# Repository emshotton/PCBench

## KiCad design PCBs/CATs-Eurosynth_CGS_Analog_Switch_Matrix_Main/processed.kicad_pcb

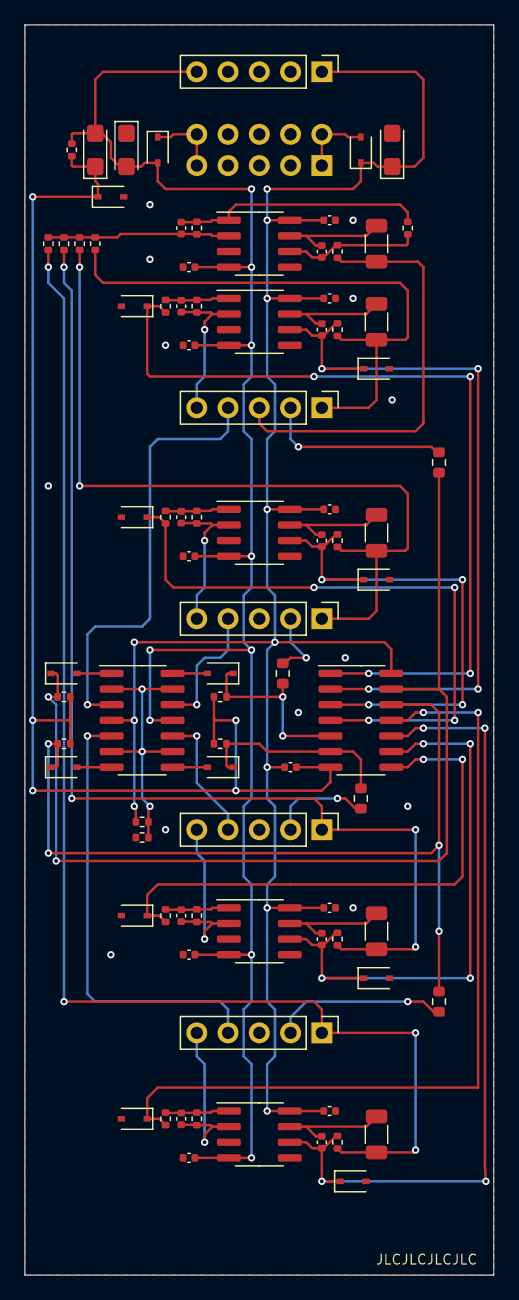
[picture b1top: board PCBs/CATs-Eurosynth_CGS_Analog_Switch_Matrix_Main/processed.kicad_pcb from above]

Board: 2 copper layers, 38.1 x 101.6 mm, 87 parts (1 on the bottom side), 52 nets.

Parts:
C1, C2, C3, C4, C13, C14, C15, C16, C21, C23: 47p; C_0402_1005Metric
C5, C6, C22: 10µF; CP_EIA-3216-18_Kemet-A
C7, C8, C9, C10, C11, C12, C17, C18, C19, C20, C24: 100n; C_0402_1005Metric
D1, D2: B5817WS; D_SOD-323
D3, D4, D5, D6, D7, D8, D9, D10, D11, D12, D13, D14, D15: 1N4148; D_SOD-323
J1: Power; Power_2x5_Vertical
J2: 1_COM; PinHeader_1x05_P2.54mm_Vertical
J3: 2; PinHeader_1x05_P2.54mm_Vertical
J4: 3; PinHeader_1x05_P2.54mm_Vertical
J5: 4; PinHeader_1x05_P2.54mm_Vertical
J6: POWER; PinHeader_1x05_P2.54mm_Vertical
R1, R2, R3, R4, R5, R6, R7, R8, R9, R10, R11, R12, R17, R19, R20, R21, R22, R23, R24, R25, R26, R31, R33, R34: 100k; R_0402_1005Metric
R13, R14, R15, R16, R35: 1k; R_1206_3216Metric
R18: 10k; R_0402_1005Metric
R27, R28, R29, R30: 1k; R_0603_1608Metric
R32: 1k; R_0402_1005Metric
U1, U2, U3, U4, U7: TL072CDT; SOIC-8_3.9x4.9mm_P1.27mm
U5: CD4066BM/TR; SOIC-14_3.9x8.7mm_P1.27mm
U6: TL074IDT; SOIC-14_3.9x8.7mm_P1.27mm

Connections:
+12V: C5.1, C7.2, C9.2, C11.2, C17.2, C19.2, C24.2, D1.1, J6.1, R17.2, U1.8, U2.8, U3.8, U4.8, U5.14, U6.4, U7.8
-12V: C6.2, C8.1, C10.1, C12.1, C18.1, C20.1, C22.2, D2.2, J6.5, R32.1, U1.4, U2.4, U3.4, U4.4, U6.11, U7.4
B1: D11.1, R19.2, R27.1, U5.13
B2: D12.1, R20.2, R28.1, U5.5
B3: D13.1, R21.2, R29.1, U5.6
B4: D14.1, R22.2, R30.1, U5.12
C1: J2.4, U6.3
C2: J3.4, U6.12
C3: J4.4, U6.10
C4: J5.4, U6.5
COMOUT: J2.3, R34.1, R35.1
GND: C5.2, C6.1, C7.1, C8.2, C9.1, C10.2, C11.1, C12.2, C17.1, C18.2, C19.1, C20.2, D3.2, D4.2, D5.2, D6.2, D7.2, D8.2, D9.2, D10.2, D15.2, J1.GND, J3.3, J4.3, J5.3, J6.2, J6.3, J6.4, R18.1, U1.3, U1.5, U2.3, U2.5, U3.3, U3.5, U4.3, U4.5, U7.3, U7.5
I1: C1.2, J2.5, R1.2, U1.2
I2: C2.2, J3.5, R2.2, U2.2
I3: C3.2, J4.5, R3.2, U3.2
I4: C4.2, J5.5, R4.2, U4.2
L1: J2.2, R27.2
L2: J3.2, R28.2
L3: J4.2, R29.2
L4: J5.2, R30.2
unnamed: C1.1, R1.1, R5.2, U1.1
unnamed: C2.1, R2.1, R6.2, U2.1
unnamed: C3.1, R3.1, R7.2, U3.1
unnamed: C4.1, R4.1, R8.2, U4.1
unnamed: C13.1, R13.2, U1.7
unnamed: C13.2, D7.1, R9.2, U1.6, U5.2
unnamed: C14.1, R14.2, U2.7
unnamed: C14.2, D8.1, R10.2, U2.6, U5.3
unnamed: C15.1, R15.2, U3.7
unnamed: C15.2, D9.1, R11.2, U3.6, U5.9
unnamed: C16.1, R16.2, U4.7
unnamed: C16.2, D10.1, R12.2, U4.6, U5.10
unnamed: C21.1, R31.1, R33.2, U7.1
unnamed: C21.2, R23.1, R24.1, R25.1, R26.1, R31.2, U7.2
unnamed: C23.1, R35.2, U7.7
unnamed: C23.2, R33.1, R34.2, U7.6
unnamed: D1.2, J1.+12V
unnamed: D2.1, J1.-12V
unnamed: D3.1, R5.1, U5.1
unnamed: D4.1, R6.1, U5.4
unnamed: D5.1, R7.1, U5.8
unnamed: D6.1, R8.1, U5.11
unnamed: D11.2, U6.1
unnamed: D12.2, U6.14
unnamed: D13.2, U6.8
unnamed: D14.2, U6.7
unnamed: R17.1, R18.2, U6.2, U6.6, U6.9, U6.13
O1: J2.1, R9.1, R13.1, R23.2
O2: J3.1, R10.1, R14.1, R24.2
O3: J4.1, R11.1, R15.1, R25.2
O4: J5.1, R12.1, R16.1, R26.2
VEE: C22.1, C24.1, D15.1, R19.1, R20.1, R21.1, R22.1, R32.2, U5.7

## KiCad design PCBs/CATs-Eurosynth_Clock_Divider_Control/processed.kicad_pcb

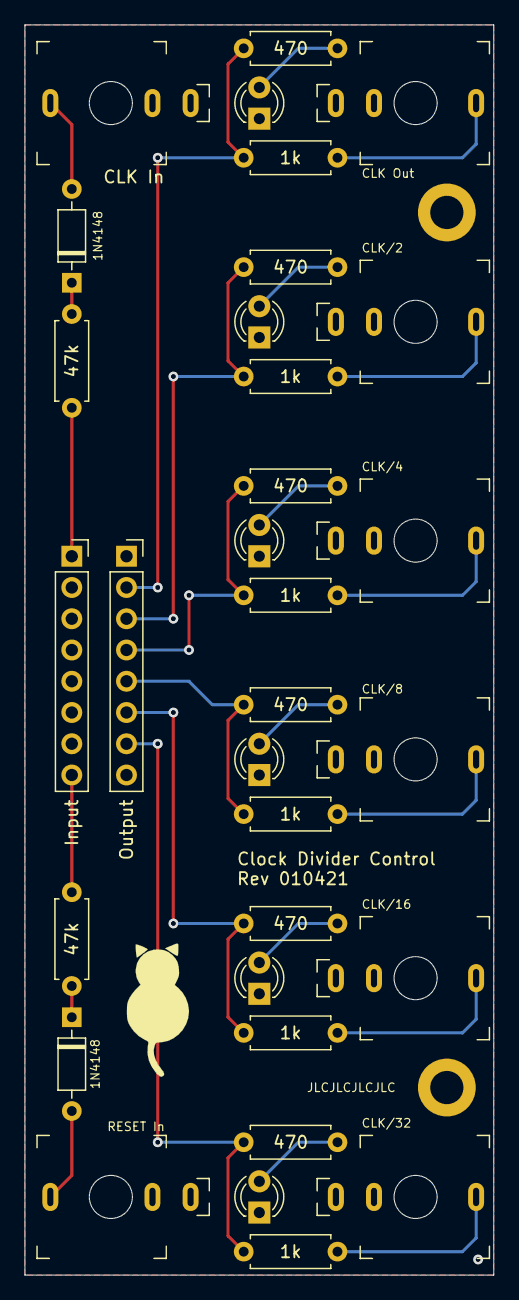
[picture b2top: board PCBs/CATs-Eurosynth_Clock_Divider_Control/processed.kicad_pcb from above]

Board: 2 copper layers, 38.1 x 101.6 mm, 34 parts (0 on the bottom side), 25 nets.

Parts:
D1, D2: 1N4148; D_DO-35_SOD27_P7.62mm_Horizontal
D4, D5, D6, D7, D8, D9: LED; LED_D3.0mm
H1, H2: MountingHole_Pad; MountingHole_2.7mm_M2.5_DIN965_Pad
J1: CLK In; PJ-301-M-12
J2: RESET In; PJ-301-M-12
J3: Input; PinSocket_1x08_P2.54mm_Vertical
J4: CLK/2; PJ-301-M-12
J5: CLK/4; PJ-301-M-12
J6: CLK/8; PJ-301-M-12
J7: CLK/16; PJ-301-M-12
J8: CLK/32; PJ-301-M-12
J9: CLK Out; PJ-301-M-12
J10: Output; PinSocket_1x08_P2.54mm_Vertical
R3, R4: 47k; R_Axial_DIN0207_L6.3mm_D2.5mm_P7.62mm_Horizontal
R17, R19, R21, R23, R25, R28: 1k; R_Axial_DIN0207_L6.3mm_D2.5mm_P7.62mm_Horizontal
R18, R20, R22, R24, R26, R29: 470; R_Axial_DIN0207_L6.3mm_D2.5mm_P7.62mm_Horizontal

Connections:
GND: D4.1, D5.1, D6.1, D7.1, D8.1, D9.1, H1.1, H2.1, J1.S, J2.S, J3.2, J3.3, J3.4, J3.5, J3.6, J3.7, J4.S, J5.S, J6.S, J7.S, J8.S, J9.S, J10.1, J10.8
unnamed: D1.1, R3.2
unnamed: D1.2, J1.T
unnamed: D2.1, R4.2
unnamed: D2.2, J2.T
unnamed: D4.2, R18.2
unnamed: D5.2, R20.2
unnamed: D6.2, R22.2
unnamed: D7.2, R24.2
unnamed: D8.2, R26.2
unnamed: D9.2, R29.2
unnamed: J3.1, R3.1
unnamed: J3.8, R4.1
unnamed: J4.T, R17.2
unnamed: J5.T, R19.2
unnamed: J6.T, R21.2
unnamed: J7.T, R23.2
unnamed: J8.T, R25.2
unnamed: J9.T, R28.2
unnamed: J10.2, R28.1, R29.1
unnamed: J10.3, R17.1, R18.1
unnamed: J10.4, R19.1, R20.1
unnamed: J10.5, R21.1, R22.1
unnamed: J10.6, R23.1, R24.1
unnamed: J10.7, R25.1, R26.1

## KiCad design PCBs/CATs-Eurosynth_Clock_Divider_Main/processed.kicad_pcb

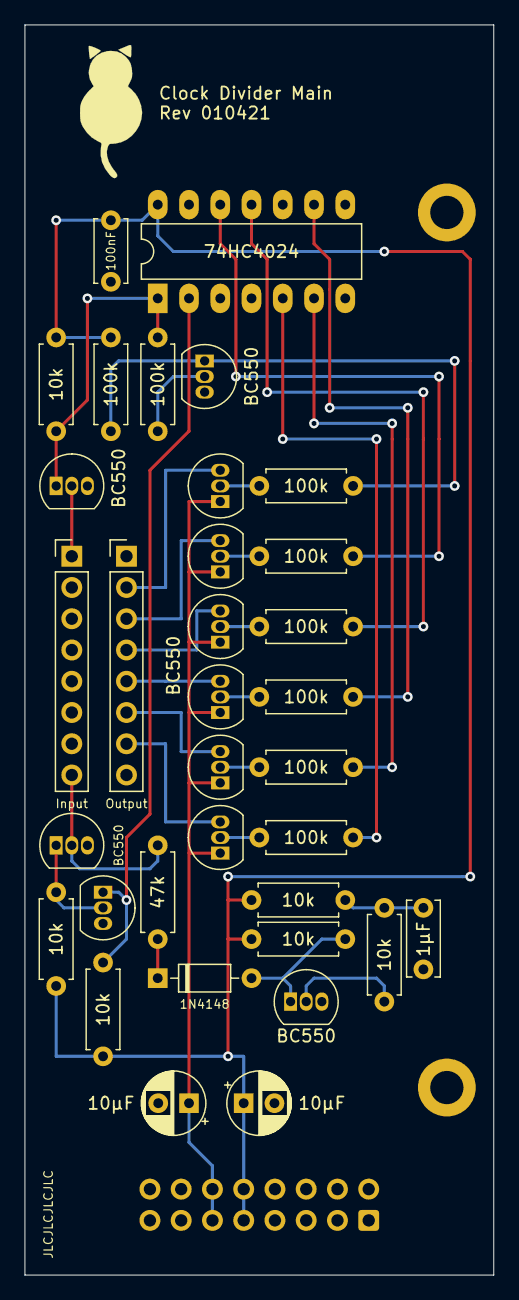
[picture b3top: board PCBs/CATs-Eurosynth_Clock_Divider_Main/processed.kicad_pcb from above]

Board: 2 copper layers, 38.1 x 101.6 mm, 37 parts (1 on the bottom side), 31 nets.

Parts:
C1: 1µF; C_Disc_D6.0mm_W2.5mm_P5.00mm
C2: 100nF; C_Disc_D5.0mm_W2.5mm_P5.00mm
C3, C5: 10µF; CP_Radial_D5.0mm_P2.50mm
D3: 1N4148; D_DO-35_SOD27_P7.62mm_Horizontal
H1, H2: MountingHole_Pad; MountingHole_2.7mm_M2.5_DIN965_Pad
J1: Input; PinHeader_1x08_P2.54mm_Vertical
J2: Output; PinHeader_1x08_P2.54mm_Vertical
J3: Power; IDC-Header_2x08_P2.54mm_Vertical
Q1, Q2, Q3, Q4, Q5, Q6, Q7, Q8, Q9, Q10, Q11: BC550; TO-92_Inline
R1, R2, R5, R6, R7, R9: 10k; R_Axial_DIN0207_L6.3mm_D2.5mm_P7.62mm_Horizontal
R8: 47k; R_Axial_DIN0207_L6.3mm_D2.5mm_P7.62mm_Horizontal
R10, R11, R12, R13, R14, R15, R16, R27: 100k; R_Axial_DIN0207_L6.3mm_D2.5mm_P7.62mm_Horizontal
U1: 74HC4024; DIP-14_W7.62mm_LongPads

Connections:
+5V: C5.1, J3.11, J3.12, Q6.1, Q7.1, Q8.1, Q9.1, Q10.1, Q11.1
+12V: C2.1, C3.1, J3.9, J3.10, R1.2, R5.2, R6.2, R7.2, R9.2, R11.2, U1.14
GND: C1.2, C2.2, C3.2, C5.2, H1.1, H2.1, J1.2, J1.3, J1.4, J1.5, J1.6, J1.7, J2.1, J2.8, J3.3, J3.4, J3.5, J3.6, J3.7, J3.8, Q1.3, Q2.3, Q3.3, Q4.3, Q5.3, U1.7
unnamed: C1.1, R1.1, R2.1
unnamed: D3.1, R8.1
unnamed: D3.2, Q1.1, R5.1
unnamed: J1.1, Q2.2
unnamed: J1.8, Q3.2, R8.2
unnamed: J2.2, Q11.3
unnamed: J2.3, Q6.3
unnamed: J2.4, Q7.3
unnamed: J2.5, Q8.3
unnamed: J2.6, Q9.3
unnamed: J2.7, Q10.3
unnamed: Q1.2, R2.2
unnamed: Q2.1, R6.1, R10.2, U1.1
unnamed: Q3.1, Q4.2, R7.1
unnamed: Q4.1, R9.1, U1.2
unnamed: Q5.1, R11.1, R27.1
unnamed: Q5.2, R10.1
unnamed: Q6.2, R12.2
unnamed: Q7.2, R13.2
unnamed: Q8.2, R14.2
unnamed: Q9.2, R15.2
unnamed: Q10.2, R16.2
unnamed: Q11.2, R27.2
unnamed: R12.1, U1.12
unnamed: R13.1, U1.11
unnamed: R14.1, U1.9
unnamed: R15.1, U1.6
unnamed: R16.1, U1.5

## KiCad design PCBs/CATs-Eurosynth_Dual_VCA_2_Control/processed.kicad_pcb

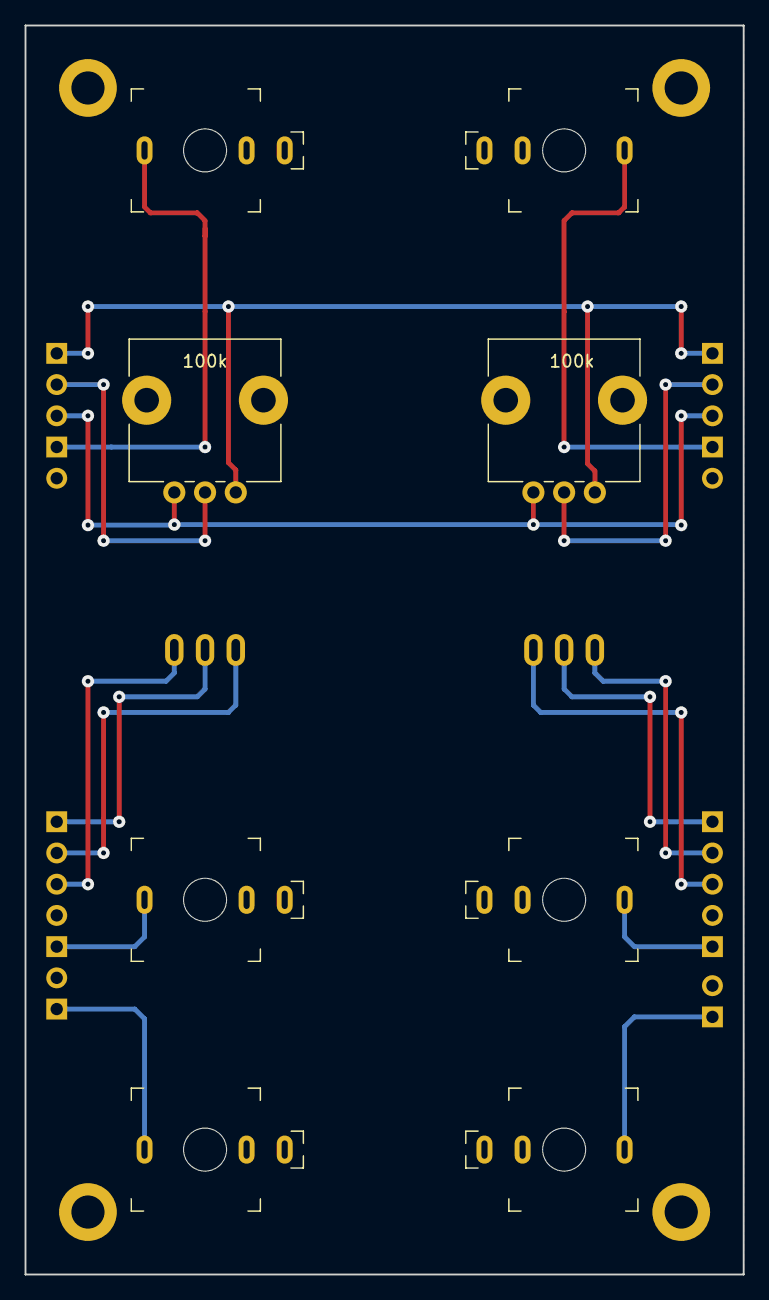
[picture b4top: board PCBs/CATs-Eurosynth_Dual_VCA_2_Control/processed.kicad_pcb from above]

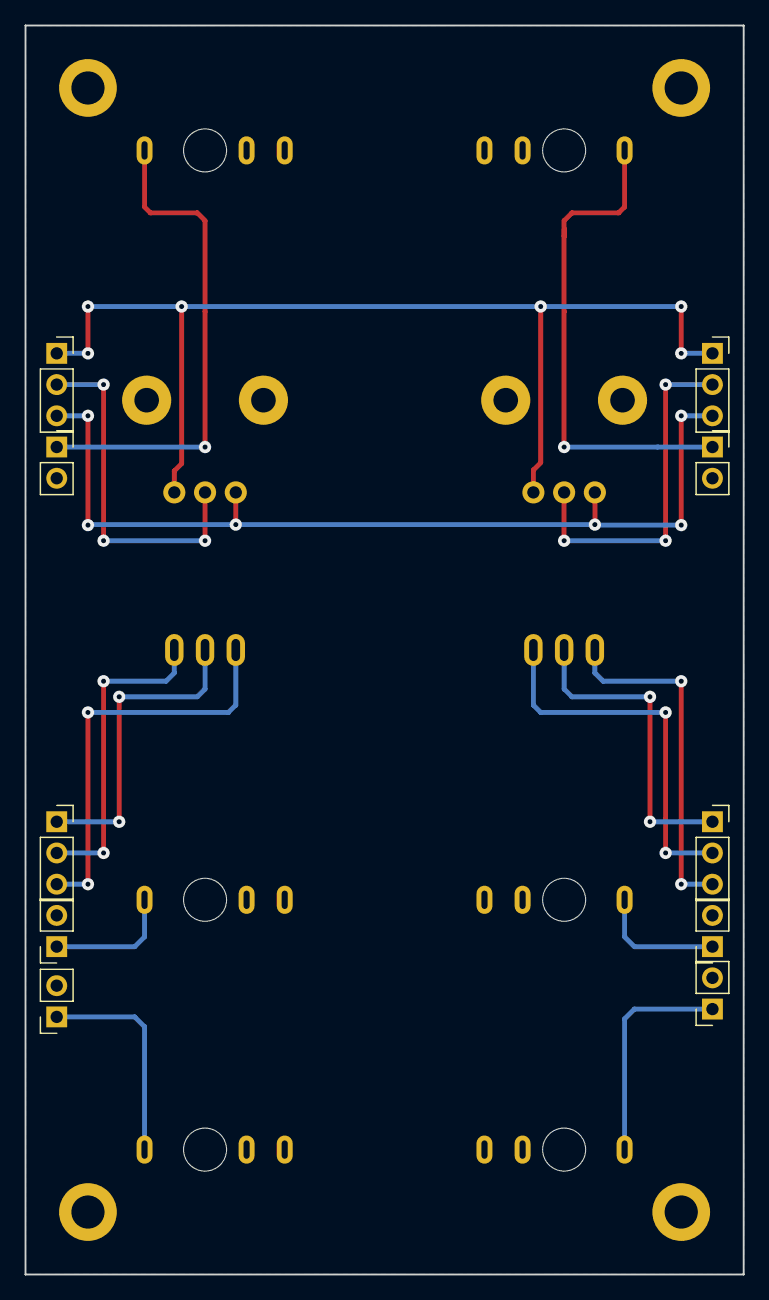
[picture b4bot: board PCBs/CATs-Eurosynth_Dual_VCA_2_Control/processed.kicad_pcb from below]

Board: 2 copper layers, 58.4 x 101.6 mm, 24 parts (10 on the bottom side), 17 nets.

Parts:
H1, H2, H3, H4: MH; MountingHole_2.7mm_M2.5_DIN965_Pad
J1: CV In #1; PJ-301-M-12
J2: Sig In #1; PJ-301-M-12
J3: Sig Out #1; PJ-301-M-12
J4: CV In #2; PJ-301-M-12
J5: Sig In #2; PJ-301-M-12
J6: Sig Out #2; PJ-301-M-12
J7: Sig Out #1; PinSocket_1x02_P2.54mm_Vertical
J8: Pot #1; PinSocket_1x03_P2.54mm_Vertical
J9: CV In #1; PinSocket_1x02_P2.54mm_Vertical
J10: Sig In #1; PinSocket_1x02_P2.54mm_Vertical
J11: SW #1; PinSocket_1x03_P2.54mm_Vertical
J12: Sig Out #2; PinSocket_1x02_P2.54mm_Vertical
J13: Pot #2; PinSocket_1x03_P2.54mm_Vertical
J14: CV In #2; PinSocket_1x02_P2.54mm_Vertical
J15: Sig In #2; PinSocket_1x02_P2.54mm_Vertical
J16: SW #2; PinSocket_1x03_P2.54mm_Vertical
R1, R21: 100k; Potentiometer_Alps_RK09L_Single_Vertical
SW1: Log/Lin #1; SMTS-1xx-Solder
SW2: Log/Lin #2; SMTS-1xx-Solder

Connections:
+12V: J8.1, J13.1, R1.1, R21.1
-12V: J8.3, J13.3, R1.3, R21.3
GND: H1.1, H2.1, H3.1, H4.1, J1.S, J2.S, J3.S, J4.S, J5.S, J6.S, J7.2, J9.2, J10.2, J12.2, J14.2, J15.2
unnamed: J1.T, J9.1
unnamed: J3.T, J7.1
unnamed: J8.2, R1.2
unnamed: J2.T, J10.1
unnamed: J11.1, SW1.1
unnamed: J11.2, SW1.2
unnamed: J11.3, SW1.3
unnamed: J6.T, J12.1
unnamed: J13.2, R21.2
unnamed: J4.T, J14.1
unnamed: J5.T, J15.1
unnamed: J16.1, SW2.1
unnamed: J16.2, SW2.2
unnamed: J16.3, SW2.3

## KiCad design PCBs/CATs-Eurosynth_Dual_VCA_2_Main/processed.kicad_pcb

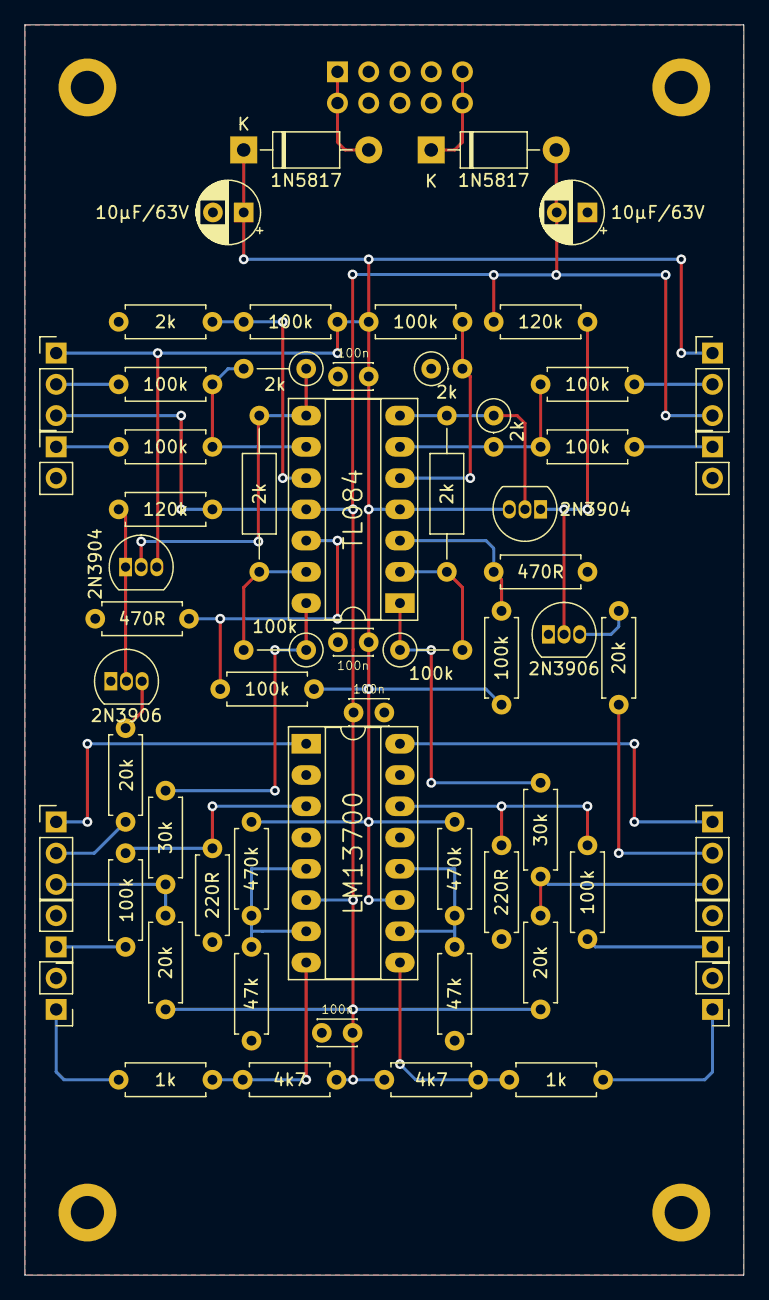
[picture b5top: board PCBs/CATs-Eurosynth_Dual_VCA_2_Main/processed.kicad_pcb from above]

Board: 2 copper layers, 58.4 x 101.6 mm, 67 parts (1 on the bottom side), 41 nets.

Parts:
C1, C2: 10µF/63V; CP_Radial_D5.0mm_P2.50mm
C3, C4, C5, C6: 100n; C_Disc_D3.0mm_W2.0mm_P2.50mm
D1, D2: 1N5817; D_DO-41_SOD81_P10.16mm_Horizontal
H1, H2, H3, H4: MH; MountingHole_2.7mm_M2.5_DIN965_Pad
IC1: TL084; DIP-14_W7.62mm_Socket_LongPads
IC2: LM13700; DIP-16_W7.62mm_Socket_LongPads
J1: Pot #1; PinHeader_1x03_P2.54mm_Vertical
J2: CV In #1; PinHeader_1x02_P2.54mm_Vertical
J3: Sig In #1; PinHeader_1x02_P2.54mm_Vertical
J4: SW #1; PinHeader_1x03_P2.54mm_Vertical
J5: Sig Out #1; PinHeader_1x02_P2.54mm_Vertical
J6: Pot #2; PinHeader_1x03_P2.54mm_Vertical
J7: Power; Power_2x5_Vertical
J8: CV In #2; PinHeader_1x02_P2.54mm_Vertical
J9: Sig In #2; PinHeader_1x02_P2.54mm_Vertical
J10: SW #2; PinHeader_1x03_P2.54mm_Vertical
J11: Sig Out #2; PinHeader_1x02_P2.54mm_Vertical
Q1, Q3: 2N3904; TO-92_Inline
Q2, Q4: 2N3906; TO-92_Inline
R2, R6, R7, R10, R17, R22, R26, R27, R30, R37: 100k; R_Axial_DIN0207_L6.3mm_D2.5mm_P7.62mm_Horizontal
R3: 2k; R_Axial_DIN0207_L6.3mm_D2.5mm_P5.08mm_Vertical
R4, R24: 2k; R_Axial_DIN0207_L6.3mm_D2.5mm_P12.70mm_Horizontal
R5, R25: 100k; R_Axial_DIN0207_L6.3mm_D2.5mm_P5.08mm_Vertical
R8: 2k; R_Axial_DIN0207_L6.3mm_D2.5mm_P7.62mm_Horizontal
R9, R29: 120k; R_Axial_DIN0207_L6.3mm_D2.5mm_P7.62mm_Horizontal
R11, R31: 470R; R_Axial_DIN0207_L6.3mm_D2.5mm_P7.62mm_Horizontal
R12, R13, R32, R33: 20k; R_Axial_DIN0207_L6.3mm_D2.5mm_P7.62mm_Horizontal
R14, R34: 30k; R_Axial_DIN0207_L6.3mm_D2.5mm_P7.62mm_Horizontal
R15, R35: 470k; R_Axial_DIN0207_L6.3mm_D2.5mm_P7.62mm_Horizontal
R16, R36: 47k; R_Axial_DIN0207_L6.3mm_D2.5mm_P7.62mm_Horizontal
R18, R38: 220R; R_Axial_DIN0207_L6.3mm_D2.5mm_P7.62mm_Horizontal
R19, R39: 4k7; R_Axial_DIN0207_L6.3mm_D2.5mm_P7.62mm_Horizontal
R20, R40: 1k; R_Axial_DIN0207_L6.3mm_D2.5mm_P7.62mm_Horizontal
R23, R28: 2k; R_Axial_DIN0207_L6.3mm_D2.5mm_P2.54mm_Vertical

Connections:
+12V: C1.1, C3.1, C4.1, D1.1, IC1.4, IC2.11, J1.1, J6.1, Q1.3, Q3.3, R7.2, R10.2, R15.2, R27.2, R30.2, R35.2
+12VA: D1.2, J7.+12V
-12V: C2.2, C5.2, C6.2, D2.2, IC1.11, IC2.6, J1.3, J6.3, R9.1, R13.1, R19.1, R29.1, R33.1, R39.1
-12VA: D2.1, J7.-12V
GND: C1.2, C2.1, C3.2, C4.2, C5.1, C6.1, H1.1, H2.1, H3.1, H4.1, IC2.4, IC2.13, J2.2, J3.2, J5.2, J7.GND, J8.2, J9.2, J11.2, Q2.1, Q4.1, R8.1, R11.1, R16.2, R18.1, R28.1, R31.1, R36.2, R38.1
unnamed: IC1.1, R25.1, R34.2
unnamed: IC1.2, R24.1, R25.2
unnamed: IC1.3, R30.1, R31.2
unnamed: IC1.5, R27.1, R28.2
unnamed: IC1.6, R22.1, R23.2, R26.1
unnamed: IC1.7, Q3.2, R23.1, R24.2
unnamed: IC1.8, Q1.2, R3.1, R4.2
unnamed: IC1.9, R2.1, R3.2, R6.1
unnamed: IC1.10, R7.1, R8.2
unnamed: IC1.12, R10.1, R11.2
unnamed: IC1.13, R4.1, R5.2
unnamed: IC1.14, R5.1, R14.2
unnamed: IC2.1, J4.1
unnamed: IC2.3, R17.1, R18.2
unnamed: IC2.5, IC2.7, R15.1, R16.1
unnamed: IC2.8, R19.2, R20.2
unnamed: IC2.9, R39.2, R40.2
unnamed: IC2.10, IC2.12, R35.1, R36.1
unnamed: IC2.14, R37.1, R38.2
unnamed: IC2.16, J10.1
unnamed: J1.2, R2.2
unnamed: J2.1, R6.2
unnamed: J3.1, R17.2
unnamed: J4.2, R12.1
unnamed: J4.3, R13.2, R14.1
unnamed: J5.1, R20.1
unnamed: J6.2, R22.2
unnamed: J8.1, R26.2
unnamed: J9.1, R37.2
unnamed: J10.2, R32.1
unnamed: J10.3, R33.2, R34.1
unnamed: J11.1, R40.1
unnamed: Q1.1, Q2.2, R9.2
unnamed: Q2.3, R12.2
unnamed: Q3.1, Q4.2, R29.2
unnamed: Q4.3, R32.2

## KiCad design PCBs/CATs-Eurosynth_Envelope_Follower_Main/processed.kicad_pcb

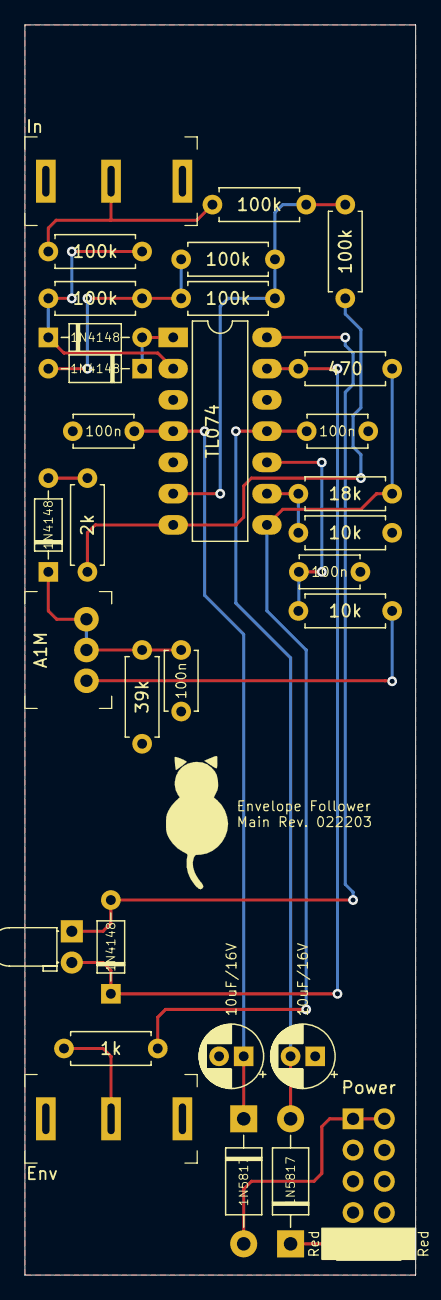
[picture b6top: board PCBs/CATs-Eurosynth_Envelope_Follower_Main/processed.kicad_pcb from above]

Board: 2 copper layers, 31.8 x 101.6 mm, 31 parts (0 on the bottom side), 20 nets.

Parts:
C1, C2, C4, C6: 100n; C_Disc_D4.7mm_W2.5mm_P5.00mm
C3, C5: 10uF/16V; CP_Radial_D5.0mm_P2.00mm
D1, D2, D3, D4: 1N4148; D_DO-35_SOD27_P7.62mm_Horizontal
D5: LED; LED_D3.0mm_Horizontal_O1.27mm_Z10.0mm
D6, D7: 1N5817; D_DO-41_SOD81_P10.16mm_Horizontal
J1: In; Jack_3.5mm_QingPu_WQP-PJ323M
J2: Env; Jack_3.5mm_QingPu_WQP-PJ323M
J3: Power; Power_2x5_Vertical
P1: A1M; Potentiometer_AlpsAlpine_RK0971110
R1, R2, R3, R4, R6, R7: 100k; R_Axial_DIN0207_L6.3mm_D2.5mm_P7.62mm_Horizontal
R5: 18k; R_Axial_DIN0207_L6.3mm_D2.5mm_P7.62mm_Horizontal
R8: 1k; R_Axial_DIN0207_L6.3mm_D2.5mm_P7.62mm_Horizontal
R9: 2k; R_Axial_DIN0207_L6.3mm_D2.5mm_P7.62mm_Horizontal
R10, R12: 10k; R_Axial_DIN0207_L6.3mm_D2.5mm_P7.62mm_Horizontal
R11: 39k; R_Axial_DIN0207_L6.3mm_D2.5mm_P7.62mm_Horizontal
R13: 470; R_Axial_DIN0207_L6.3mm_D2.5mm_P7.62mm_Horizontal
U1: TL074; DIP-14_W7.62mm_LongPads

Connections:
+12V: C3.1, C4.1, D6.1 (K), U1.4 (V+)
-12V: C5.2, C6.2, D7.2 (A), U1.11 (V-)
GND: C1.2, C2.2, C3.2, C4.2, C5.1, C6.1, J1.S, J1.TN, J2.S, J3.GND, R11.1, R12.1, U1.3 (+), U1.5 (+), U1.12 (+)
unnamed: C1.1, D3.1 (K), P1.CCW, P1.W, R11.2
unnamed: C2.1, R10.2, U1.10 (+)
unnamed: D1.1 (K), R2.1, R6.2, U1.2 (-)
unnamed: D1.2 (A), D2.1 (K), U1.1
unnamed: D2.2 (A), R2.2, R3.1, R7.1
unnamed: D3.2 (A), R9.2
unnamed: D4.1 (K), D5.2 (A), R13.2, U1.13 (-)
unnamed: D4.2 (A), D5.1 (K), U1.14
unnamed: D6.2 (A), J3.+12V
unnamed: D7.1 (K), J3.-12V
unnamed: J1.T, R1.1, R6.1
unnamed: J2.T, R8.2
unnamed: P1.CW, R10.1
unnamed: R1.2, R3.2, R4.1, R7.2, U1.6 (-)
unnamed: R4.2, R9.1, U1.7
unnamed: R5.1, R12.2, U1.9 (-)
unnamed: R5.2, R8.1, R13.1, U1.8

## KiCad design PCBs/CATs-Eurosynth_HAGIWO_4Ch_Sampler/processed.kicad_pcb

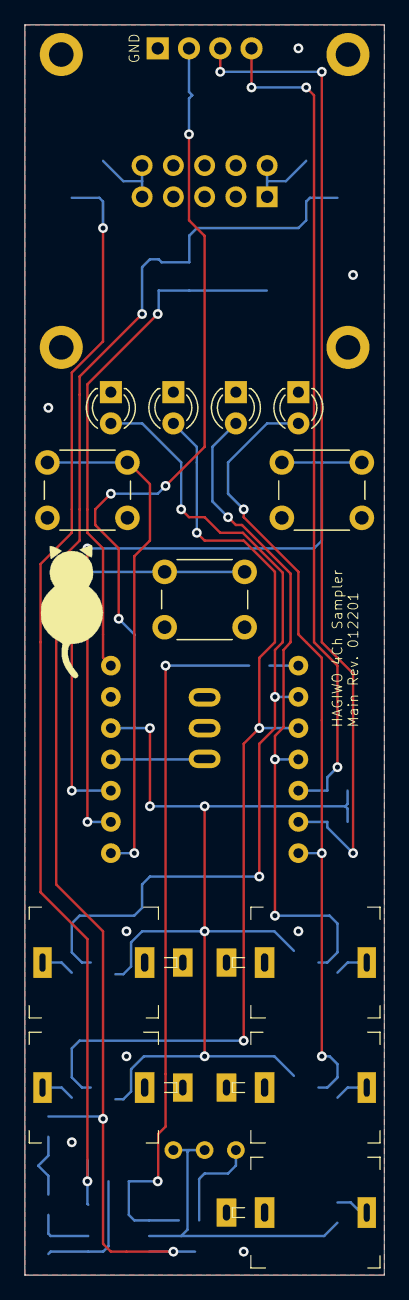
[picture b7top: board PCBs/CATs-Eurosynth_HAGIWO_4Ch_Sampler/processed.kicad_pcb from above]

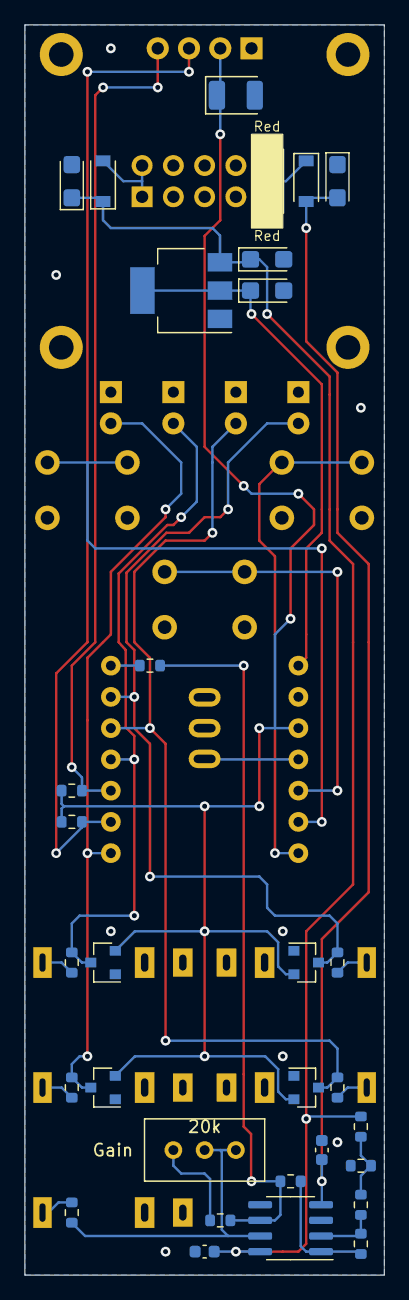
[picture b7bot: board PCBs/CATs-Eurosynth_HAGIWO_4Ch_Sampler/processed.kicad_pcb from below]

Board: 2 copper layers, 29.2 x 101.6 mm, 46 parts (32 on the bottom side), 29 nets.

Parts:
C1: 100uF/6.3V; CP_EIA-3528-21_Kemet-B
C3, C4, C5, C7: 10uF/16V; CP_EIA-3216-18_Kemet-A
C6, C8: 100n; C_0603_1608Metric
D1, D2, D5, D6: BAV99; SOT-23
D3: Ch 1; LED_D3.0mm
D4: Ch 3; LED_D3.0mm
D7: Ch 2; LED_D3.0mm
D8: Ch 4; LED_D3.0mm
D9, D10: B5819W SL; D_SOD-123
DISP1: MC096xx; 0.96inch_OLED_MC096GX
J1: Ch. 1 In; Jack_3.5mm_QingPu_WQP-PJ301M-12
J2: Ch. 3 In; Jack_3.5mm_QingPu_WQP-PJ301M-12
J3: Ch. 2 In; Jack_3.5mm_QingPu_WQP-PJ301M-12
J4: Ch. 4 In; Jack_3.5mm_QingPu_WQP-PJ301M-12
J5: Out; Jack_3.5mm_QingPu_WQP-PJ301M-12
J6: Power; Power_2x5_Vertical
R1, R2: 3k3; R_0603_1608Metric
R3, R4, R7, R8: 33k; R_0603_1608Metric
R5: 7k5; R_0603_1608Metric
R6, R9, R10, R13: 10k; R_0603_1608Metric
R11: 27k; R_0603_1608Metric
R12: 1k5; R_0603_1608Metric
R14: 1k; R_0603_1608Metric
SW1: Left; SW_PUSH_6mm
SW2: Right; SW_PUSH_6mm
SW3: Down; SW_PUSH_6mm
SW4: Mode; SMTS-1xx-Solder
T1: 20k; Potentiometer_Bourns_3296W_Vertical
U1: TL072CDT; SOIC-8_3.9x4.9mm_P1.27mm
U2: SeeeduinoXIAOPin; Seeeduino XIAO Pin
U3: AMS1117-5.0; SOT-223-3_TabPin2

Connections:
+3V3: C1.1, D1.2, D2.2, D5.2, D6.2, DISP1.VCC, R1.2, R2.2, U2.12
+5V: C5.1, U2.14, U3.2
+12V: C3.1, C4.1, C6.2, D9.1, R5.2, U1.8, U3.3
-12V: C7.2, C8.1, D10.2, U1.4
A7: SW1.1, U2.8
A8: SW2.1, U2.9
A9: SW3.1, U2.10
D1: D1.3, D3.2, R3.1, U2.2
D2: D5.3, D7.2, R7.1, U2.3
D3: D2.3, D4.2, R4.1, U2.4
D4: D6.3, D8.2, R8.1, U2.7
D10: SW4.2, U2.11
DAC: R13.2, U2.1
GND: C1.2, C3.2, C4.2, C5.2, C6.1, C7.1, C8.2, D1.1, D2.1, D3.1, D4.1, D5.1, D6.1, D7.1, D8.1, DISP1.GND, J1.S, J1.TN, J2.S, J2.TN, J3.S, J3.TN, J4.S, J4.TN, J5.S, J6.GND, R12.1, SW1.2, SW2.2, SW3.2, SW4.1, U1.3, U1.5, U2.13, U3.1
unnamed: D9.2, J6.+12V
unnamed: D10.1, J6.-12V
unnamed: J1.T, R3.2
unnamed: J2.T, R4.2
unnamed: J3.T, R7.2
unnamed: J4.T, R8.2
unnamed: J5.T, R14.1
unnamed: R6.2, R9.1, U1.2
unnamed: R10.1, R11.2, R13.1, U1.6
unnamed: R6.1, R10.2, U1.1
unnamed: R11.1, T1.1
unnamed: R5.1, R9.2, R12.2
unnamed: R14.2, T1.2, T1.3, U1.7
SCL: DISP1.SCL, R2.1, U2.6
SDA: DISP1.SDA, R1.1, U2.5

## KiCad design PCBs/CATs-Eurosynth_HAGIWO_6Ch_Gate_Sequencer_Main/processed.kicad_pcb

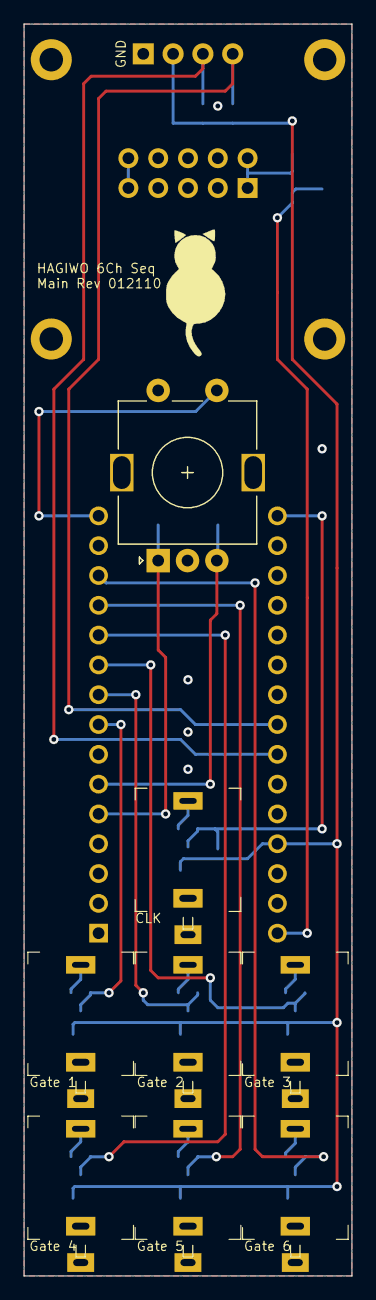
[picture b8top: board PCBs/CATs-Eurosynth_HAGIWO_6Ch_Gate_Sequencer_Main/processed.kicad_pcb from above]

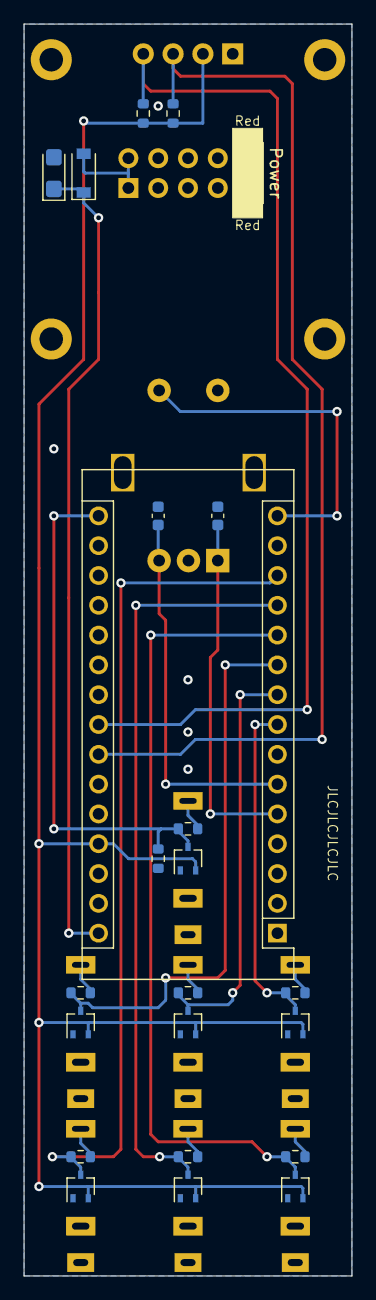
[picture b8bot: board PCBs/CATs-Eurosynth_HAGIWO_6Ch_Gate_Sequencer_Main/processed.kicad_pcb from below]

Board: 2 copper layers, 27.9 x 106.7 mm, 32 parts (23 on the bottom side), 23 nets.

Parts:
A1: Arduino_Nano_v3.x; Arduino_Nano
C1: 10µF/16V; CP_EIA-3216-18_Kemet-A
C7, C8: 10n; C_0603_1608Metric
D1: B5817W; D_SOD-123
D2, D3, D4, D5, D6, D7, D8: BAV99W; SOT-323_SC-70
DISP1: MC096xx; MC096Gx
J1: Power; Power_2x5_Vertical
J2: Gate 2; Jack_3.5mm_QingPu_WQP-PJ301M-12
J3: CLK; Jack_3.5mm_QingPu_WQP-PJ301M-12
J4: Gate 1; Jack_3.5mm_QingPu_WQP-PJ301M-12
J5: Gate 3; Jack_3.5mm_QingPu_WQP-PJ301M-12
J6: Gate 4; Jack_3.5mm_QingPu_WQP-PJ301M-12
J7: Gate 5; Jack_3.5mm_QingPu_WQP-PJ301M-12
J8: Gate 6; Jack_3.5mm_QingPu_WQP-PJ301M-12
R1, R4, R5, R6, R8, R9, R10: 470R; R_0603_1608Metric
R2: 100k; R_0603_1608Metric
R3, R7: 3k3; R_0603_1608Metric
SW2: Encoder; RotaryEncoder_Alps_EC11E-Switch_Vertical_H20mm

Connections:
+5V: A1.27, D2.2, D3.2, D4.2, D5.2, D6.2, D7.2, D8.2, DISP1.VCC, R3.2, R7.2
+12V: A1.30, C1.1, D1.1
+12VA: D1.2, J1.+12V
CLK: A1.16, D2.3, R1.1, R2.2
ENC_A: A1.5, C7.1, SW2.A
ENC_B: A1.6, C8.1, SW2.B
ENC_SW: A1.15, SW2.S1
G1: A1.8, D3.3, R4.2
G2: A1.9, D4.3, R5.2
G3: A1.10, D5.3, R6.2
G4: A1.11, D6.3, R8.2
G5: A1.12, D7.3, R9.2
G6: A1.13, D8.3, R10.2
GND: A1.4, A1.29, C1.2, C7.2, C8.2, D2.1, D3.1, D4.1, D5.1, D6.1, D7.1, D8.1, DISP1.GND, J1.GND, J2.S, J3.S, J3.TN, J4.S, J5.S, J6.S, J7.S, J8.S, R2.1, SW2.C, SW2.S2
unnamed: J2.T, R5.1
unnamed: J3.T, R1.2
unnamed: J4.T, R4.1
unnamed: J5.T, R6.1
unnamed: J6.T, R8.1
unnamed: J7.T, R9.1
unnamed: J8.T, R10.1
SCL: A1.24, DISP1.SCL, R7.1
SDA: A1.23, DISP1.SDA, R3.1
